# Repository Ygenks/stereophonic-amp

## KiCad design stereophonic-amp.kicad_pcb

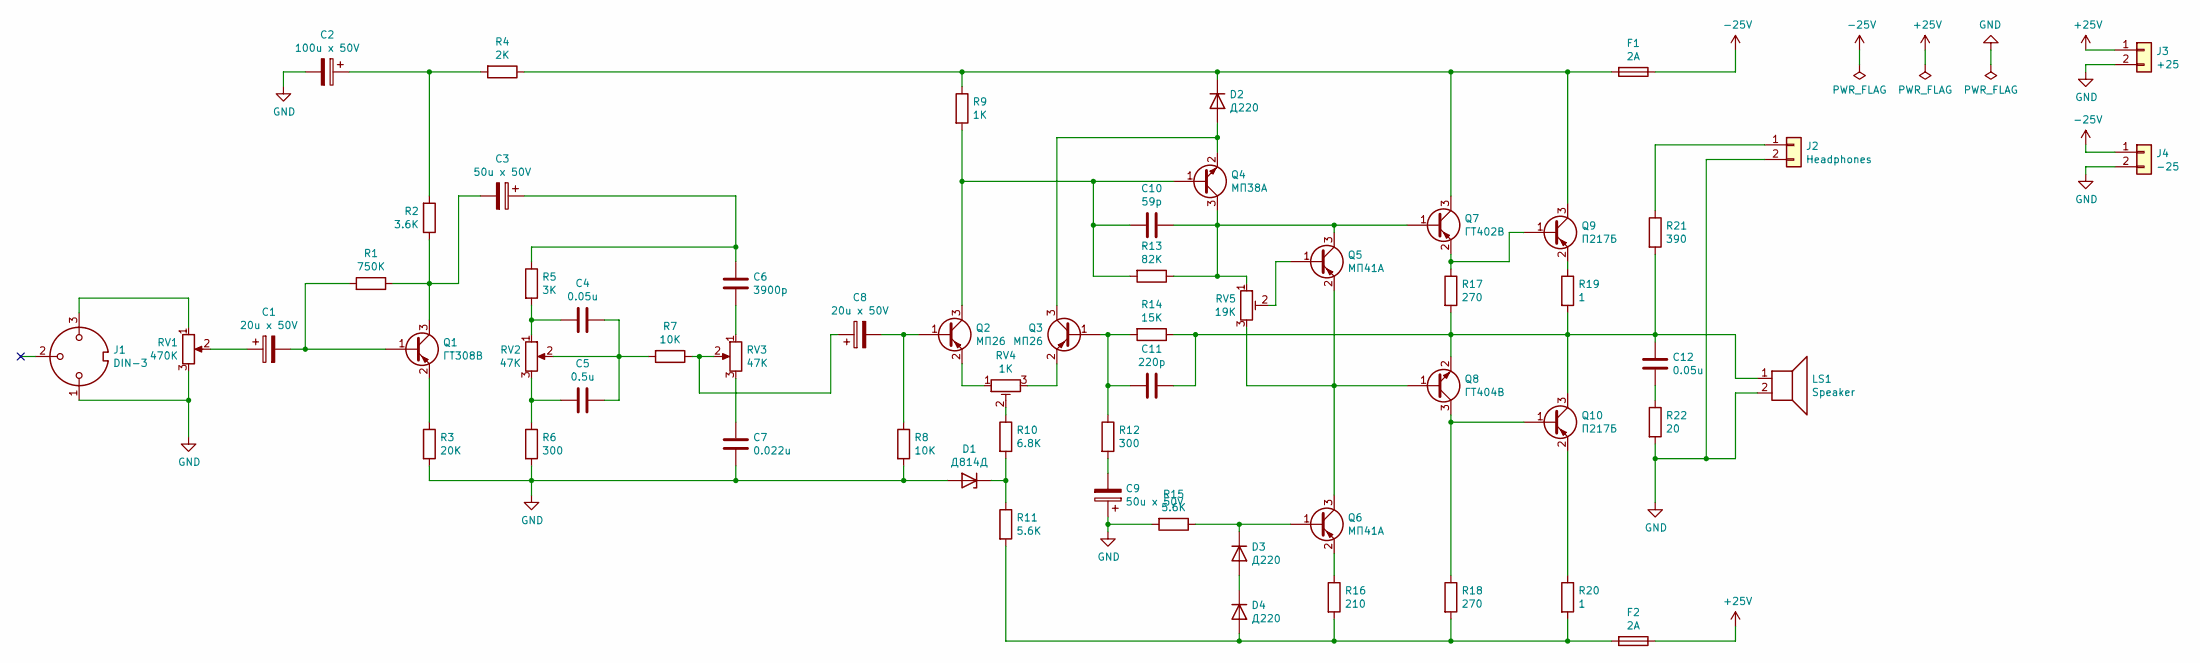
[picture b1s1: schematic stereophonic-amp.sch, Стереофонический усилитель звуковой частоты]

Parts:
C1, C8: 20u x 50V; CP_Radial_D5.0mm_P2.00mm
C2: 100u x 50V; CP_Radial_D6.3mm_P2.50mm
C3, C9: 50u x 50V; CP_Radial_D6.3mm_P2.50mm
C4, C12: 0.05u; C_Rect_L4.6mm_W3.8mm_P2.50mm_MKS02_FKP02
C5: 0.5u; C_Rect_L7.0mm_W4.5mm_P5.00mm
C6: 3900p; C_Rect_L4.6mm_W3.8mm_P2.50mm_MKS02_FKP02
C7: 0.022u; C_Rect_L4.6mm_W3.8mm_P2.50mm_MKS02_FKP02
C10: 59p; C_Rect_L7.0mm_W4.5mm_P5.00mm
C11: 220p; C_Rect_L7.0mm_W4.5mm_P5.00mm
D1: Д814Д; D_DO-15_P15.24mm_Horizontal
D2, D3, D4: Д220; D_A-405_P12.70mm_Horizontal
F1, F2: 2А; Fuseholder_Cylinder-5x20mm_Stelvio-Kontek_PTF78_Horizontal_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
J1: DIN-3; PinHeader_1x03_P2.54mm_Vertical
J2: Headphones; PinHeader_1x02_P2.54mm_Vertical
J3: +25; PinHeader_1x02_P2.54mm_Vertical
J4: -25; PinHeader_1x02_P2.54mm_Vertical
LS1: Speaker; PinHeader_1x02_P2.54mm_Vertical
Q1: ГТ308В; TO-11-3
Q2, Q3: МП26; TO-11-3
Q4: МП38А; TO-11-3
Q5: МП41А; TO-11-3
Q6: МП41А; PinHeader_1x03_P2.54mm_Vertical
Q7: ГТ402В; TO-11-3
Q8: ГТ404В; TO-11-3
Q9, Q10: П217Б; PinHeader_1x03_P2.54mm_Vertical
R1: 750K; R_Axial_DIN0207_L6.3mm_D2.5mm_P10.16mm_Horizontal
R2: 3.6K; R_Axial_DIN0207_L6.3mm_D2.5mm_P10.16mm_Horizontal
R3: 20K; R_Axial_DIN0207_L6.3mm_D2.5mm_P10.16mm_Horizontal
R4: 2K; R_Axial_DIN0207_L6.3mm_D2.5mm_P10.16mm_Horizontal
R5: 3K; R_Axial_DIN0207_L6.3mm_D2.5mm_P10.16mm_Horizontal
R6, R12: 300; R_Axial_DIN0207_L6.3mm_D2.5mm_P10.16mm_Horizontal
R7, R8: 10K; R_Axial_DIN0207_L6.3mm_D2.5mm_P10.16mm_Horizontal
R9: 1K; R_Axial_DIN0207_L6.3mm_D2.5mm_P10.16mm_Horizontal
R10: 6.8K; R_Axial_DIN0207_L6.3mm_D2.5mm_P10.16mm_Horizontal
R11, R15: 5.6K; R_Axial_DIN0207_L6.3mm_D2.5mm_P10.16mm_Horizontal
R13: 82K; R_Axial_DIN0207_L6.3mm_D2.5mm_P10.16mm_Horizontal
R14: 15K; R_Axial_DIN0207_L6.3mm_D2.5mm_P10.16mm_Horizontal
R16: 210; R_Axial_DIN0207_L6.3mm_D2.5mm_P10.16mm_Horizontal
R17, R18: 270; R_Axial_DIN0207_L6.3mm_D2.5mm_P10.16mm_Horizontal
R19, R20: 1; R_Axial_DIN0414_L11.9mm_D4.5mm_P20.32mm_Horizontal
R21: 390; R_Axial_DIN0207_L6.3mm_D2.5mm_P10.16mm_Horizontal
R22: 20; R_Axial_DIN0309_L9.0mm_D3.2mm_P12.70mm_Horizontal
RV1: 470K; PinHeader_1x03_P2.54mm_Vertical
RV2, RV3: 47K; PinHeader_1x03_P2.54mm_Vertical
RV4: 1K; Potentiometer_Piher_PT-10-V10_Vertical
RV5: 19K; Potentiometer_Piher_PT-10-V10_Vertical

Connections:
+25V: F2.1, J3.1
-25V: F1.1, J4.1
GND: C2.2, C7.2, C9.1, D1.2 (A), J1.1, J2.2, J3.2, J4.2, LS1.2, R3.2, R6.2, R8.2, R15.2, R22.2, RV1.3
unnamed: C1.1, RV1.2
unnamed: C1.2, Q1.1 (B), R1.2
unnamed: C2.1, R2.2, R4.2
unnamed: C3.1, C6.1, R5.1
unnamed: C3.2, Q1.3 (C), R1.1, R2.1
unnamed: C4.1, C5.1, R7.2, RV2.2
unnamed: C4.2, R5.2, RV2.1
unnamed: C5.2, R6.1, RV2.3
unnamed: C6.2, RV3.1
unnamed: C7.1, RV3.3
unnamed: C8.1, R7.1, RV3.2
unnamed: C8.2, Q2.1 (B), R8.1
unnamed: C9.2, R12.2
unnamed: C10.1, Q4.3 (C), Q5.3 (C), Q7.1 (B), R13.1, RV5.1
unnamed: C10.2, Q2.3 (C), Q4.1 (B), R9.2, R13.2
unnamed: C11.1, C12.1, LS1.1, Q8.2 (E), Q10.3 (C), R14.1, R17.2, R19.2, R21.2
unnamed: C11.2, Q3.1 (B), R12.1, R14.2
unnamed: C12.2, R22.1
unnamed: D1.1 (K), R10.2, R11.1
unnamed: D2.1 (K), F1.2, Q7.3 (C), Q9.3 (C), R4.1, R9.1
unnamed: D2.2 (A), Q3.3 (C), Q4.2 (E)
unnamed: D3.1 (K), Q6.1 (B), R15.1
unnamed: D3.2 (A), D4.1 (K)
unnamed: D4.2 (A), F2.2, R11.2, R16.2, R18.2, R20.2
unnamed: J1.3, RV1.1
unnamed: J2.1, R21.1
unnamed: Q1.2 (E), R3.1
unnamed: Q2.2 (E), RV4.1
unnamed: Q3.2 (E), RV4.3
unnamed: Q5.1 (B), RV5.2
unnamed: Q5.2 (E), Q6.3 (C), Q8.1 (B), RV5.3
unnamed: Q6.2 (E), R16.1
unnamed: Q7.2 (E), Q9.1 (B), R17.1
unnamed: Q9.2 (E), R19.1
unnamed: Q8.3 (C), Q10.1 (B), R18.1
unnamed: Q10.2 (E), R20.1
unnamed: R10.1, RV4.2

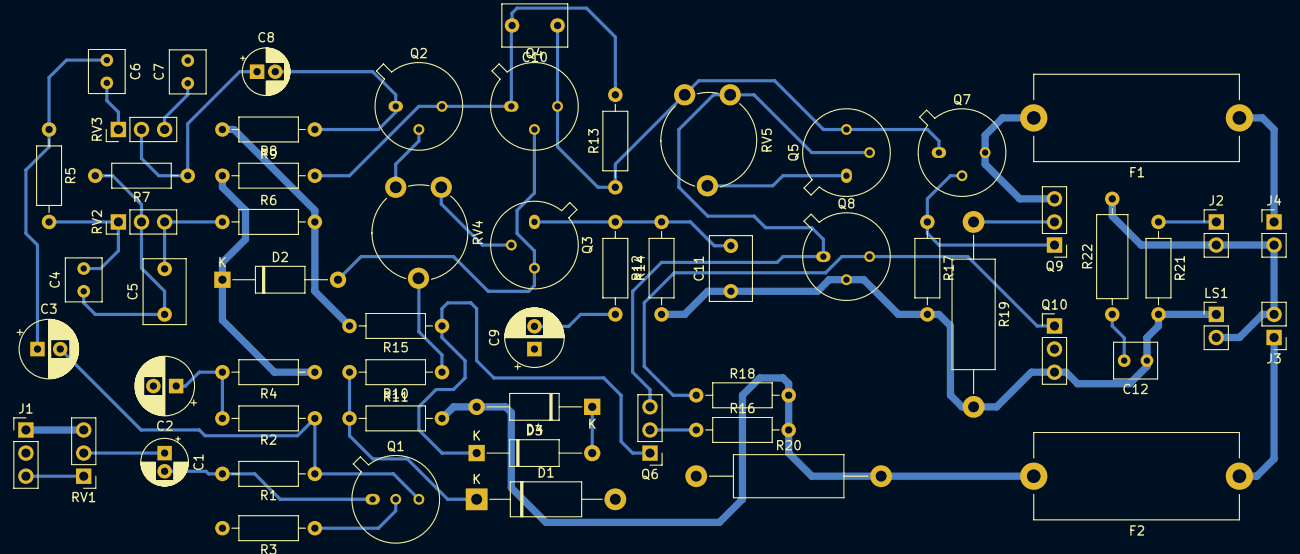
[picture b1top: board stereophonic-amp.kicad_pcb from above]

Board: 2 copper layers, 60 parts (0 on the bottom side), 40 nets.

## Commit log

2021-05-31 Finish schematic
2021-05-31 Finished preamp
2021-06-01 Route tone control block
2021-06-02 Trace first cascades of amplifier
2021-06-02 Finish routing pcb
